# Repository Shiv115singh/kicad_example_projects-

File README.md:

## References
## Acknowledgment
This project is intended for learning and skill development in PCB design.  
It was implemented using KiCad, with support from online learning resources including YouTube tutorials and technical documentation available on Google.
it is created for learning purposes only.

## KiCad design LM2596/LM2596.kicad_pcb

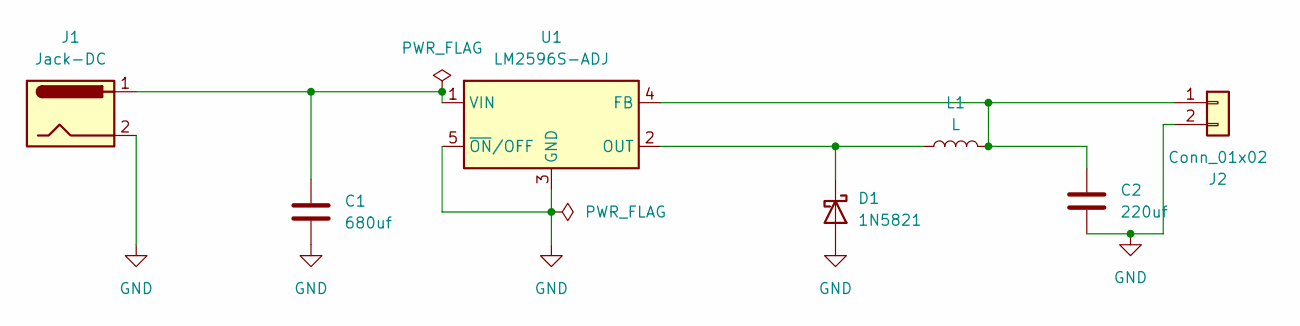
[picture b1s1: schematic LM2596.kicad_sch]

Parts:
C1: 680uf; C_0805_2012Metric
C2: 220uf; C_0805_2012Metric
D1: 1N5821; D_DO-201AD_P12.70mm_Horizontal
J1: Jack-DC; BarrelJack_SwitchcraftConxall_RAPC10U_Horizontal
J2: Conn_01x02; TerminalBlock_Phoenix_MKDS-1,5-2_1x02_P5.00mm_Horizontal
L1: L; L_APV_APH0420
U1: LM2596S-ADJ; TO-263-5_TabPin3

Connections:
GND: C1.2, C2.2, D1.2 (A), J1.2, J2.2, U1.3 (GND), U1.5 (~ON/OFF)
unnamed: D1.1 (K), L1.1, U1.2 (OUT)
unnamed: C2.1, J2.1, L1.2, U1.4 (FB)
unnamed: C1.1, J1.1, U1.1 (VIN)

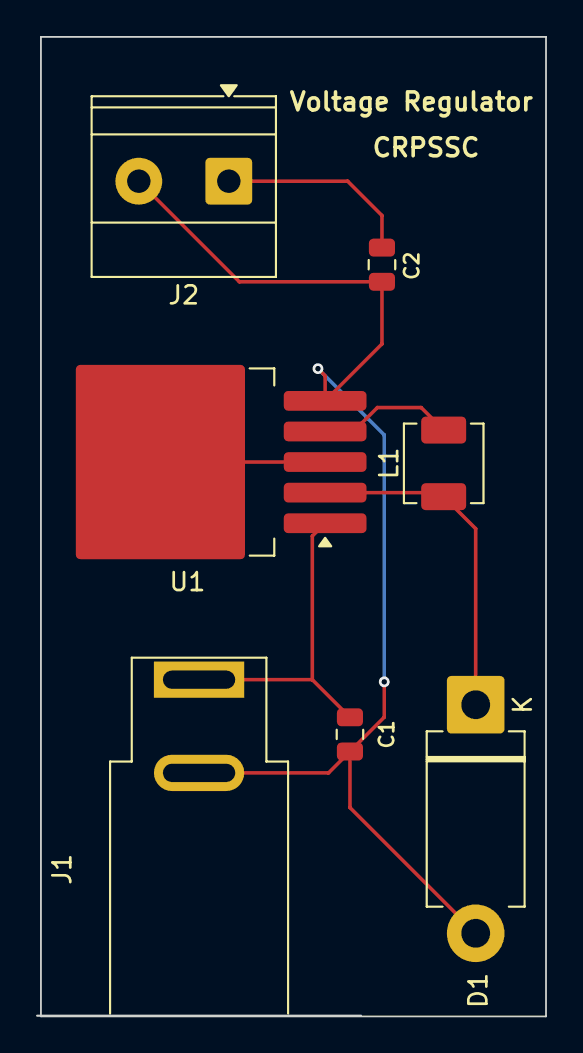
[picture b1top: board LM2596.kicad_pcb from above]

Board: 2 copper layers, 28.1 x 54.4 mm, 7 parts (0 on the bottom side), 4 nets.

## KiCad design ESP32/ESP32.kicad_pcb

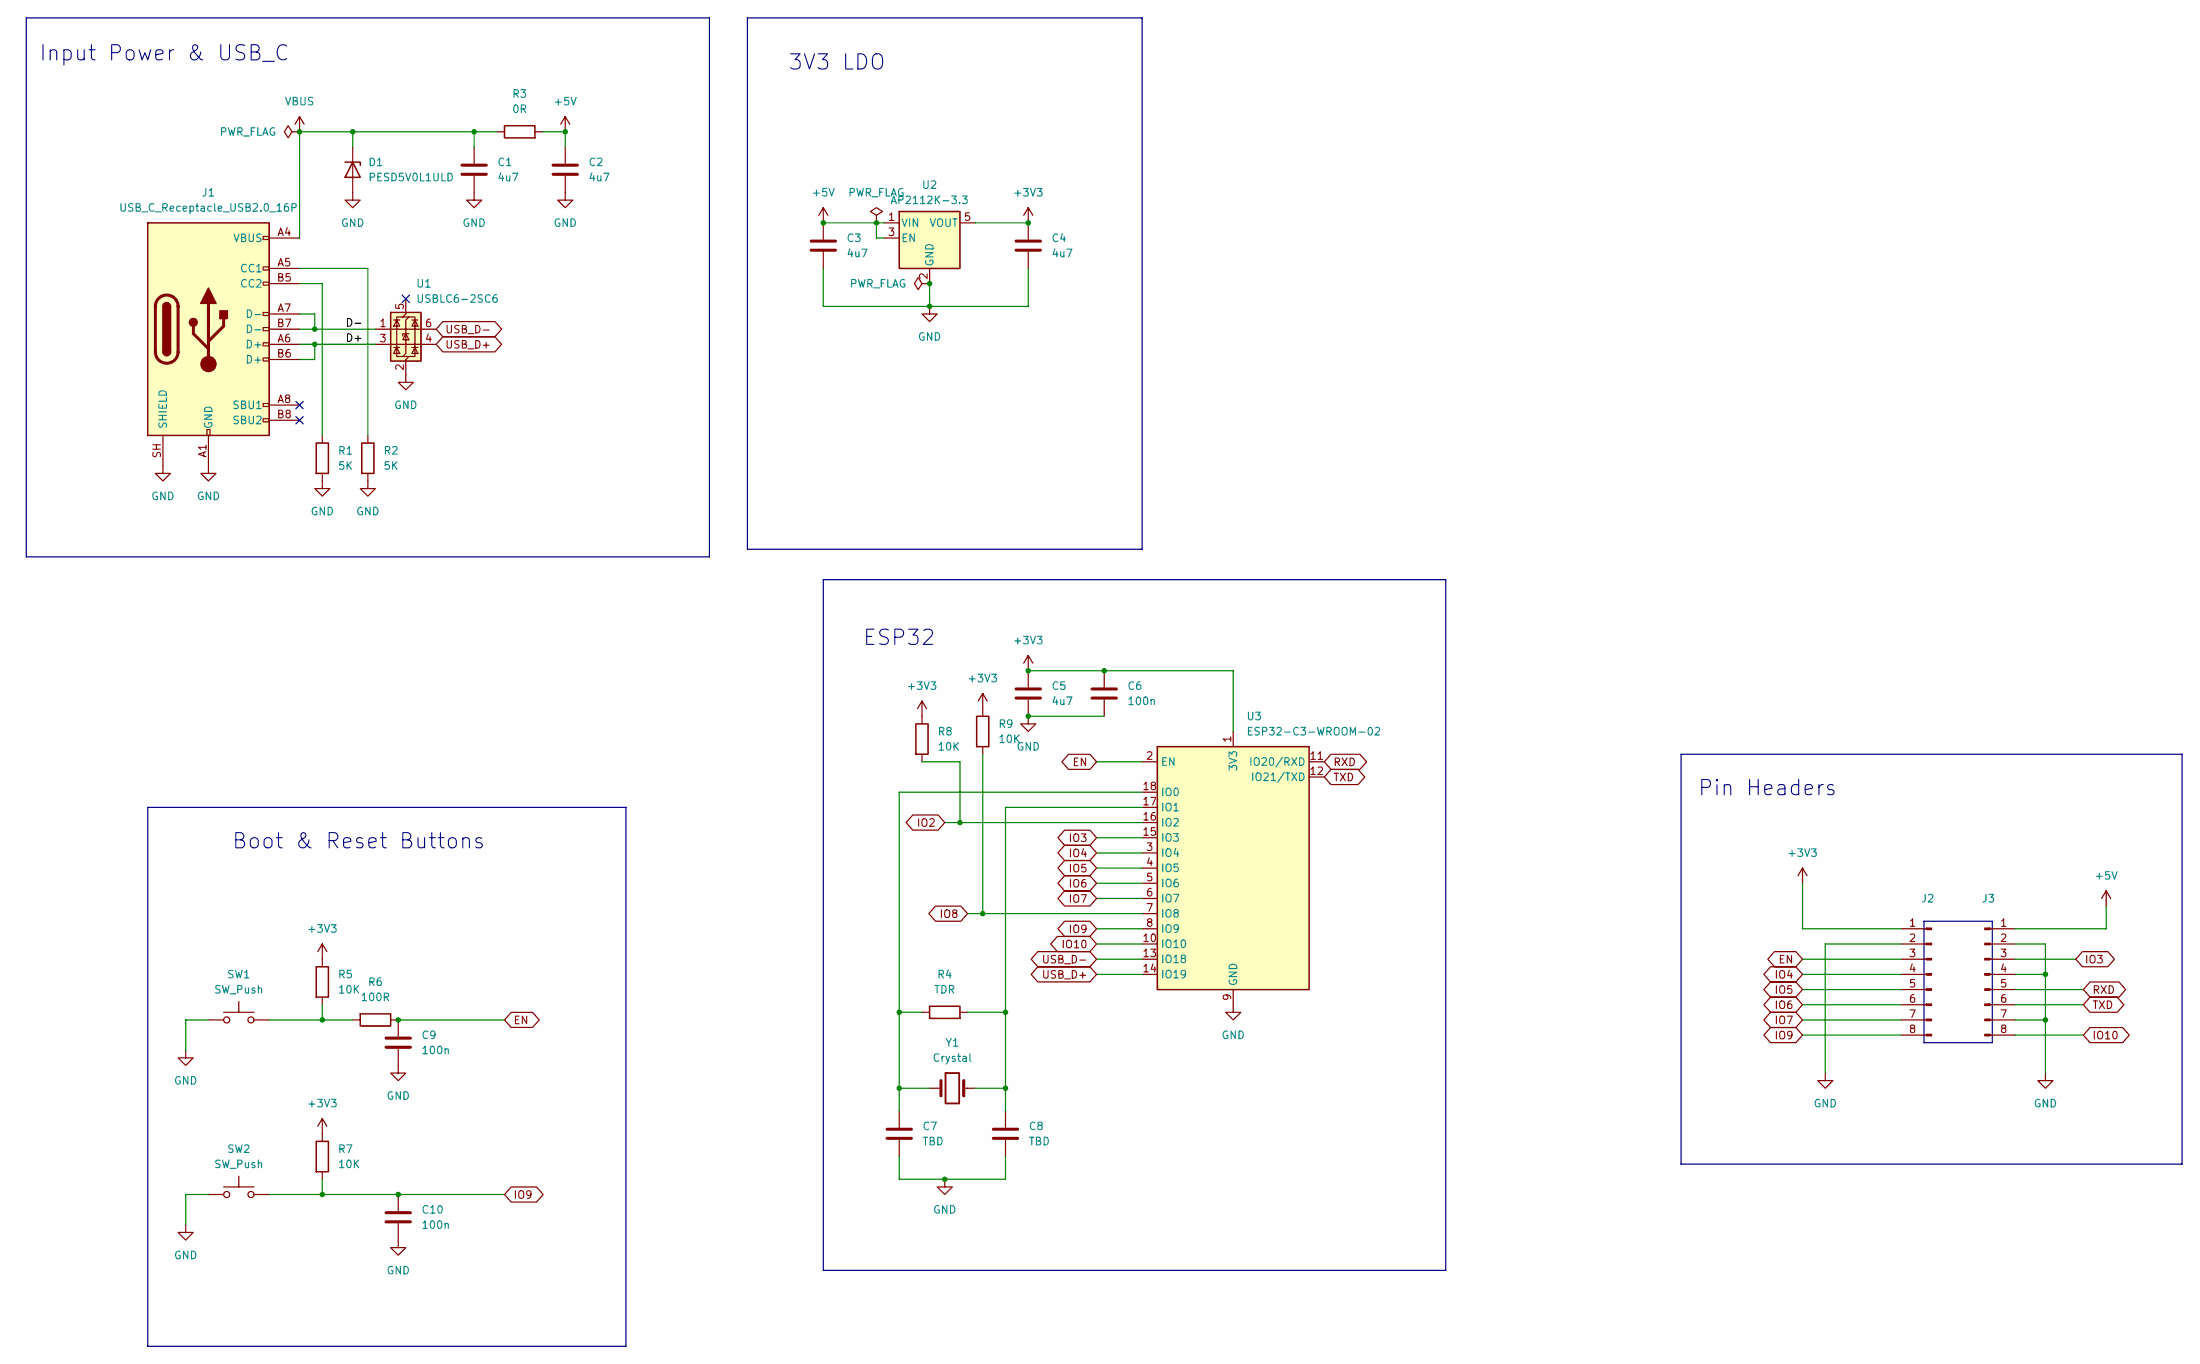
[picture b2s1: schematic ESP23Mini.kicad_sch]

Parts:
C1, C2, C3, C4, C5: 4u7; C_0805_2012Metric
C6, C9, C10: 100n; C_0402_1005Metric
C7, C8: TBD; C_0201_0603Metric
D1: PESD5V0L1ULD; D_SOD-882D
J1: USB_C_Receptacle_USB2.0_16P; USB_C_Receptacle_G-Switch_GT-USB-7010ASV
J2, J3: Conn_01x08_Pin; PinHeader_1x08_P2.54mm_Vertical
R1, R2: 5K; R_0402_1005Metric
R3: 0R; R_0805_2012Metric
R4: TDR; R_0201_0603Metric
R5, R7, R8, R9: 10K; R_0402_1005Metric
R6: 100R; R_0402_1005Metric
SW1, SW2: SW_Push; SW_SPST_B3U-1000P
U1: USBLC6-2SC6; SOT-23-6
U2: AP2112K-3.3; SOT-23-5
U3: ESP32-C3-WROOM-02
Y1: Crystal; Crystal_SMD_3215-2Pin_3.2x1.5mm

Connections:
+3V3: C4.1, C5.1, C6.1, J2.1, R5.1, R7.1, R8.1, R9.1, U2.5 (VOUT), U3.1 (3V3)
+5V: C2.1, C3.1, J3.1, R3.2, U2.1 (VIN), U2.3 (EN)
/ESP32-C3-Mini/D+: J1.A6 (D+), J1.B6 (D+), U1.3 (I/O2)
/ESP32-C3-Mini/D-: J1.A7 (D-), J1.B7 (D-), U1.1 (I/O1)
EN: C9.1, J2.3, R6.1, U3.2 (EN)
GND: C1.2, C2.2, C3.2, C4.2, C5.2, C6.2, C7.2, C8.2, C9.2, C10.2, D1.2 (A), J1.A1 (GND), J1.A12 (GND), J1.B1 (GND), J1.B12 (GND), J1.SH (SHIELD), J2.2, J3.2, J3.4, J3.7, R1.2, R2.2, SW1.1, SW2.1, U1.2 (GND), U2.2 (GND), U3.9 (GND), U3.19 (GND)
IO2: R8.2, U3.16 (IO2)
IO3: J3.3, U3.15 (IO3)
IO4: J2.4, U3.3 (IO4)
IO5: J2.5, U3.4 (IO5)
IO6: J2.6, U3.5 (IO6)
IO7: J2.7, U3.6 (IO7)
IO8: R9.2, U3.7 (IO8)
IO9: C10.1, J2.8, R7.2, SW2.2, U3.8 (IO9)
IO10: J3.8, U3.10 (IO10)
unnamed: J1.A5 (CC1), R2.1
unnamed: J1.B5 (CC2), R1.1
unnamed: R5.2, R6.2, SW1.2
unnamed: C7.1, R4.1, U3.18 (IO0), Y1.1
unnamed: C8.1, R4.2, U3.17 (IO1), Y1.2
RXD: J3.5, U3.11 (IO20/RXD)
TXD: J3.6, U3.12 (IO21/TXD)
USB_D+: U1.4 (I/O2), U3.14 (IO19)
USB_D-: U1.6 (I/O1), U3.13 (IO18)
VBUS: C1.1, D1.1 (K), J1.A4 (VBUS), J1.A9 (VBUS), J1.B4 (VBUS), J1.B9 (VBUS), R3.1

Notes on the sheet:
Input Power & USB_C
ESP32
Boot & Reset Buttons
3V3 LDO
Pin Headers

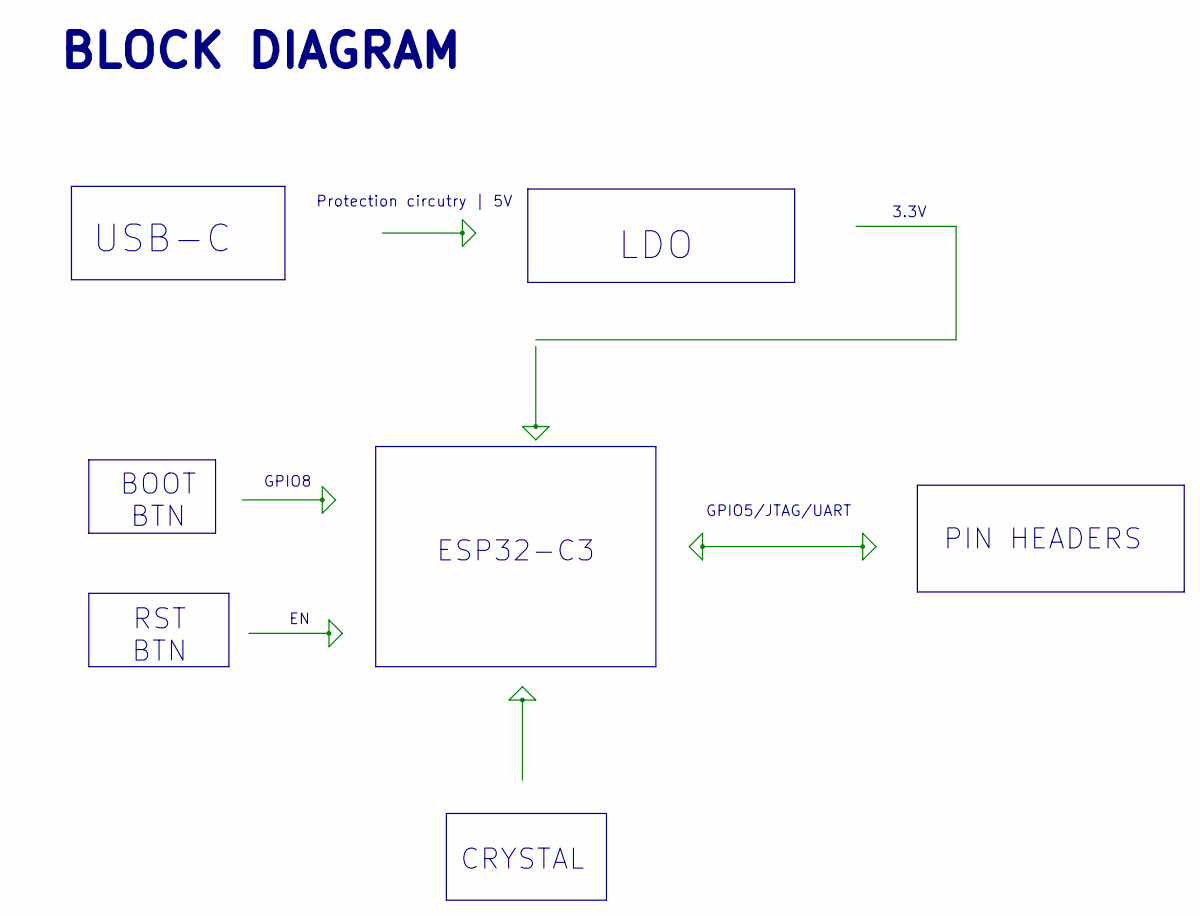
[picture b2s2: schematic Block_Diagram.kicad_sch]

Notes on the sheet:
GPIO5/JTAG/UART
BOOT BTN
LDO
CRYSTAL
BLOCK DIAGRAM
PIN HEADERS
3.3V
RST BTN
Protection circutry | 5V
USB-C
GPIO8
ESP32-C3

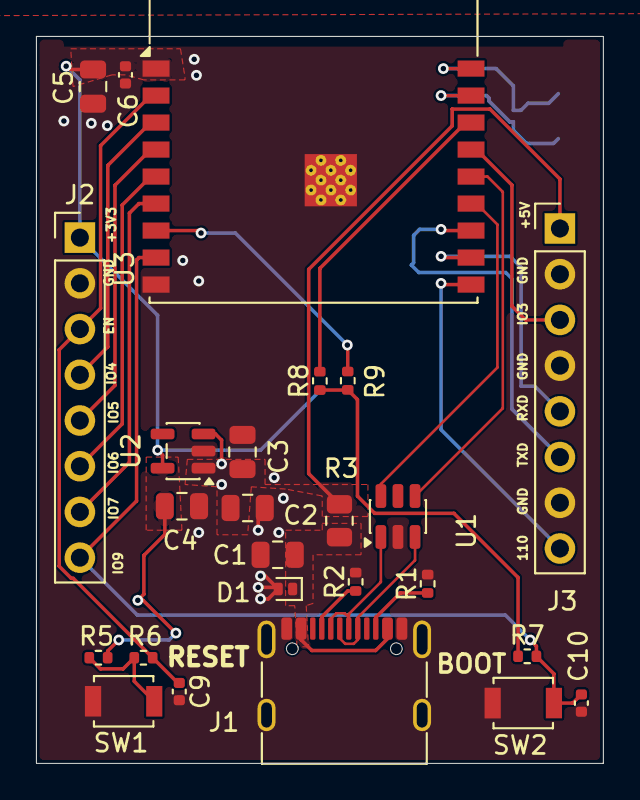
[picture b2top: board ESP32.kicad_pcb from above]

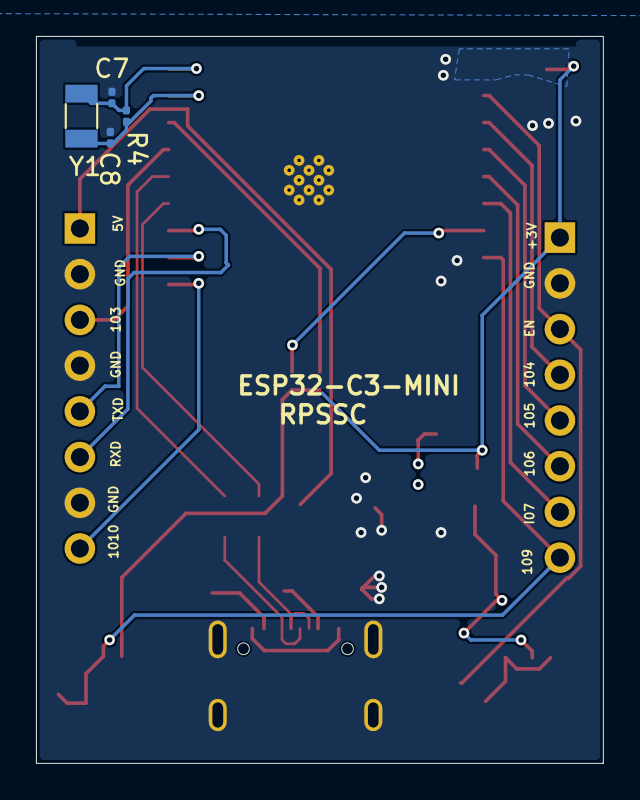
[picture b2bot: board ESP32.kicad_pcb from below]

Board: 4 copper layers, 31.5 x 40.4 mm, 29 parts (4 on the bottom side), 25 nets.

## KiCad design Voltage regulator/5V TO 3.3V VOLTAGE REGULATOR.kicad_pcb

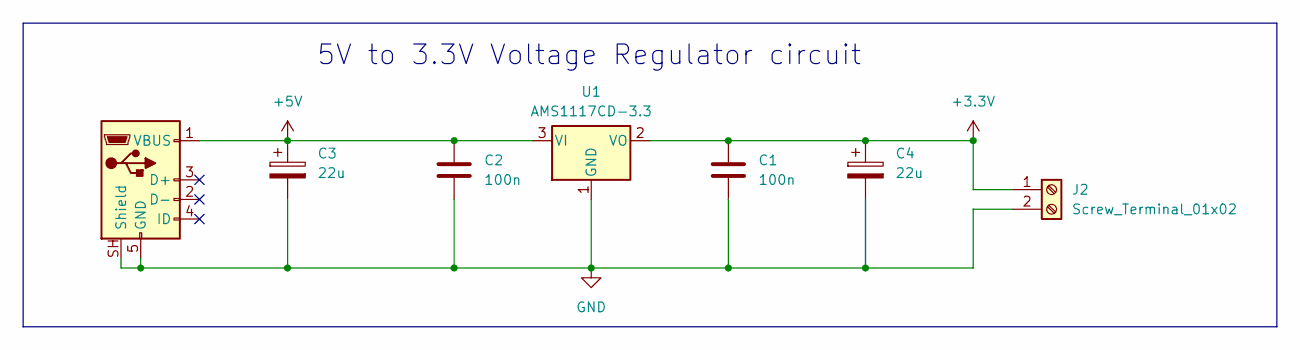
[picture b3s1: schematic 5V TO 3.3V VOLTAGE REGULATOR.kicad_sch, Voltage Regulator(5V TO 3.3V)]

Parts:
C1, C2: 100n; C_0402_1005Metric
C3, C4: 22u; CP_Elec_6.3x7.7
J1: USB_B_Micro; USB_Micro-B_Molex_47346-0001
J2: Screw_Terminal_01x02; TerminalBlock_Phoenix_MKDS-1,5-2-5.08_1x02_P5.08mm_Horizont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
U1: AMS1117CD-3.3; TO-252-3_TabPin2

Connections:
+3.3V: C1.1, C4.1, J2.1, U1.2 (VO)
+5V: C2.1, C3.1, J1.1 (VBUS), U1.3 (VI)
GND: C1.2, C2.2, C3.2, C4.2, J1.5 (GND), J1.SH (Shield), J2.2, U1.1 (GND)

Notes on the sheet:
5V to 3.3V Voltage Regulator circuit

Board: 2 copper layers, 7 parts (0 on the bottom side), 3 nets, no tracks yet.

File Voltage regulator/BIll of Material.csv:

"Id";"Designator";"Footprint";"Quantity";"Designation";"Supplier and ref";
1;"C1, C2";"C_0402_1005Metric";2;"100n";;;
2;"C3, C4";"CP_Elec_6.3x7.7";2;"22u";;;
3;"J1";"USB_Micro-B_Molex_47346-0001";1;"USB_B_Micro";;;
4;"J2";"TerminalBlock_Phoenix_MKDS-1,5-2-5.08_1x02_P5.08mm_Horizontal";1;"Screw_Terminal_01x02";;;
5;"U1";"TO-252-3_TabPin2";1;"AMS1117CD-3.3";;;

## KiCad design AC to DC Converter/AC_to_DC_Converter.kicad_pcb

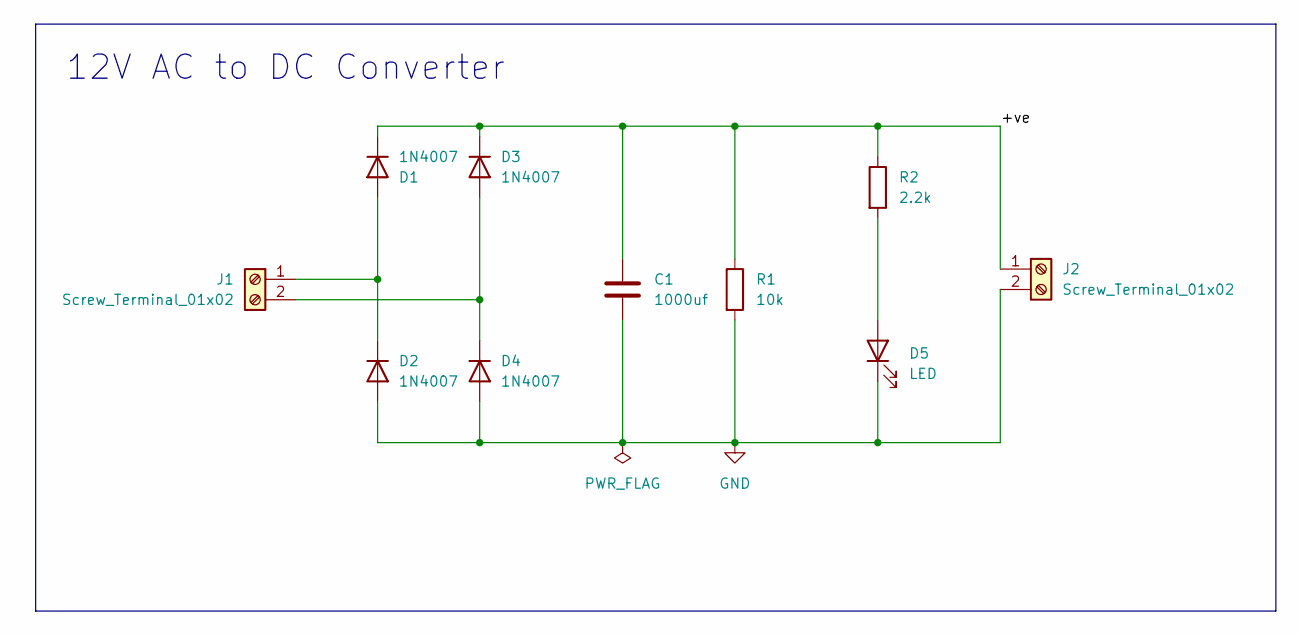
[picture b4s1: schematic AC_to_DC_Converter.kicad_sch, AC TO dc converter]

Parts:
C1: 1000uf; C_Radial_D8.0mm_H11.5mm_P3.50mm
D1, D2, D3, D4: 1N4007; D_DO-41_SOD81_P10.16mm_Horizontal
D5: LED; LED_D5.0mm
J1, J2: Screw_Terminal_01x02; TerminalBlock_Phoenix_MKDS-1,5-2-5.08_1x02_P5.08mm_Horizont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
R1: 10k; R_Axial_DIN0207_L6.3mm_D2.5mm_P15.24mm_Horizontal
R2: 2.2k; R_Axial_DIN0207_L6.3mm_D2.5mm_P15.24mm_Horizontal

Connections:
/+ve: C1.1, D1.1 (K), D3.1 (K), J2.1, R1.1, R2.1
GND: C1.2, D2.2 (A), D4.2 (A), D5.1 (K), J2.2, R1.2
unnamed: D1.2 (A), D2.1 (K), J1.1
unnamed: D3.2 (A), D4.1 (K), J1.2
unnamed: D5.2 (A), R2.2

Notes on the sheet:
12V AC to DC Converter

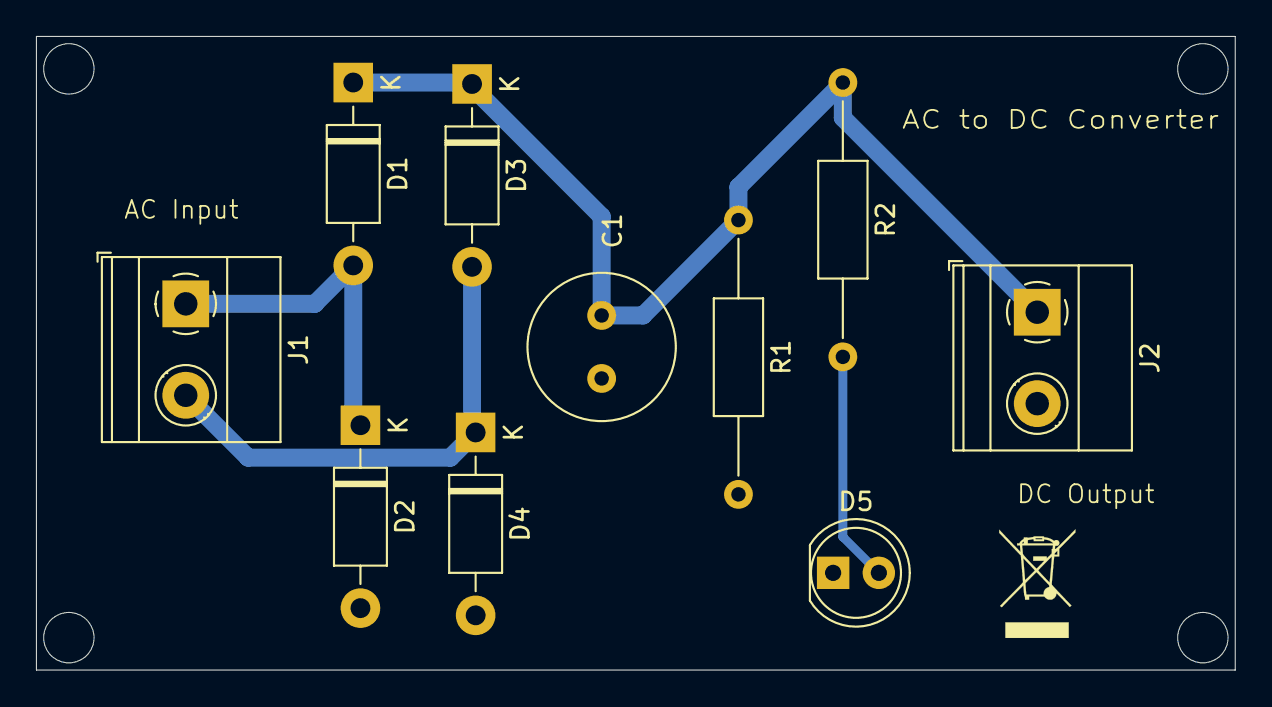
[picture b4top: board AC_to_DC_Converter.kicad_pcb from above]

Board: 2 copper layers, 66.6 x 35.2 mm, 10 parts (0 on the bottom side), 5 nets.

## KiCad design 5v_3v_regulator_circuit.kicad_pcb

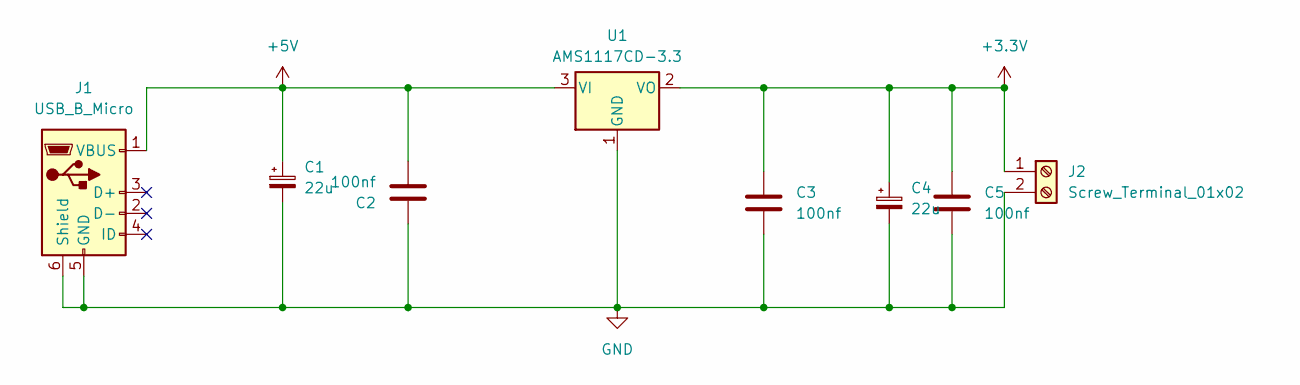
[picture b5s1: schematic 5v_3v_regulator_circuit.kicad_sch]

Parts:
C1, C4: 22u; C_01005_0402Metric
C2, C3, C5: 100nf; CP_Elec_6.3x5.7
J1: USB_B_Micro; USB_Micro-B_Amphenol_10118194-0001LF_Horizontal
J2: Screw_Terminal_01x02; TerminalBlock_Phoenix_MKDS-1,5-2-5.08_1x02_P5.08mm_Horizont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
U1: AMS1117CD-3.3; TO-252-3_TabPin2

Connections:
+3.3V: C3.1, C4.1, C5.1, J2.1, U1.2 (VO)
+5V: C1.1, C2.2, J1.1 (VBUS), U1.3 (VI)
GND: C1.2, C2.1, C3.2, C4.2, C5.2, J1.5 (GND), J1.6 (Shield), J2.2, U1.1 (GND)

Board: 2 copper layers, 8 parts (0 on the bottom side), 3 nets, no tracks yet.

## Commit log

2026-02-02 Create Rectifier
2026-02-02 Rectifier
2026-02-04 Create power supply
2026-04-22 Create Basic
2026-04-22 Create ideal diode
2026-04-24 Create Project
2026-04-24 Create References
2026-04-24 Update README with references and acknowledgment
    Added references and acknowledgment sections to README.
